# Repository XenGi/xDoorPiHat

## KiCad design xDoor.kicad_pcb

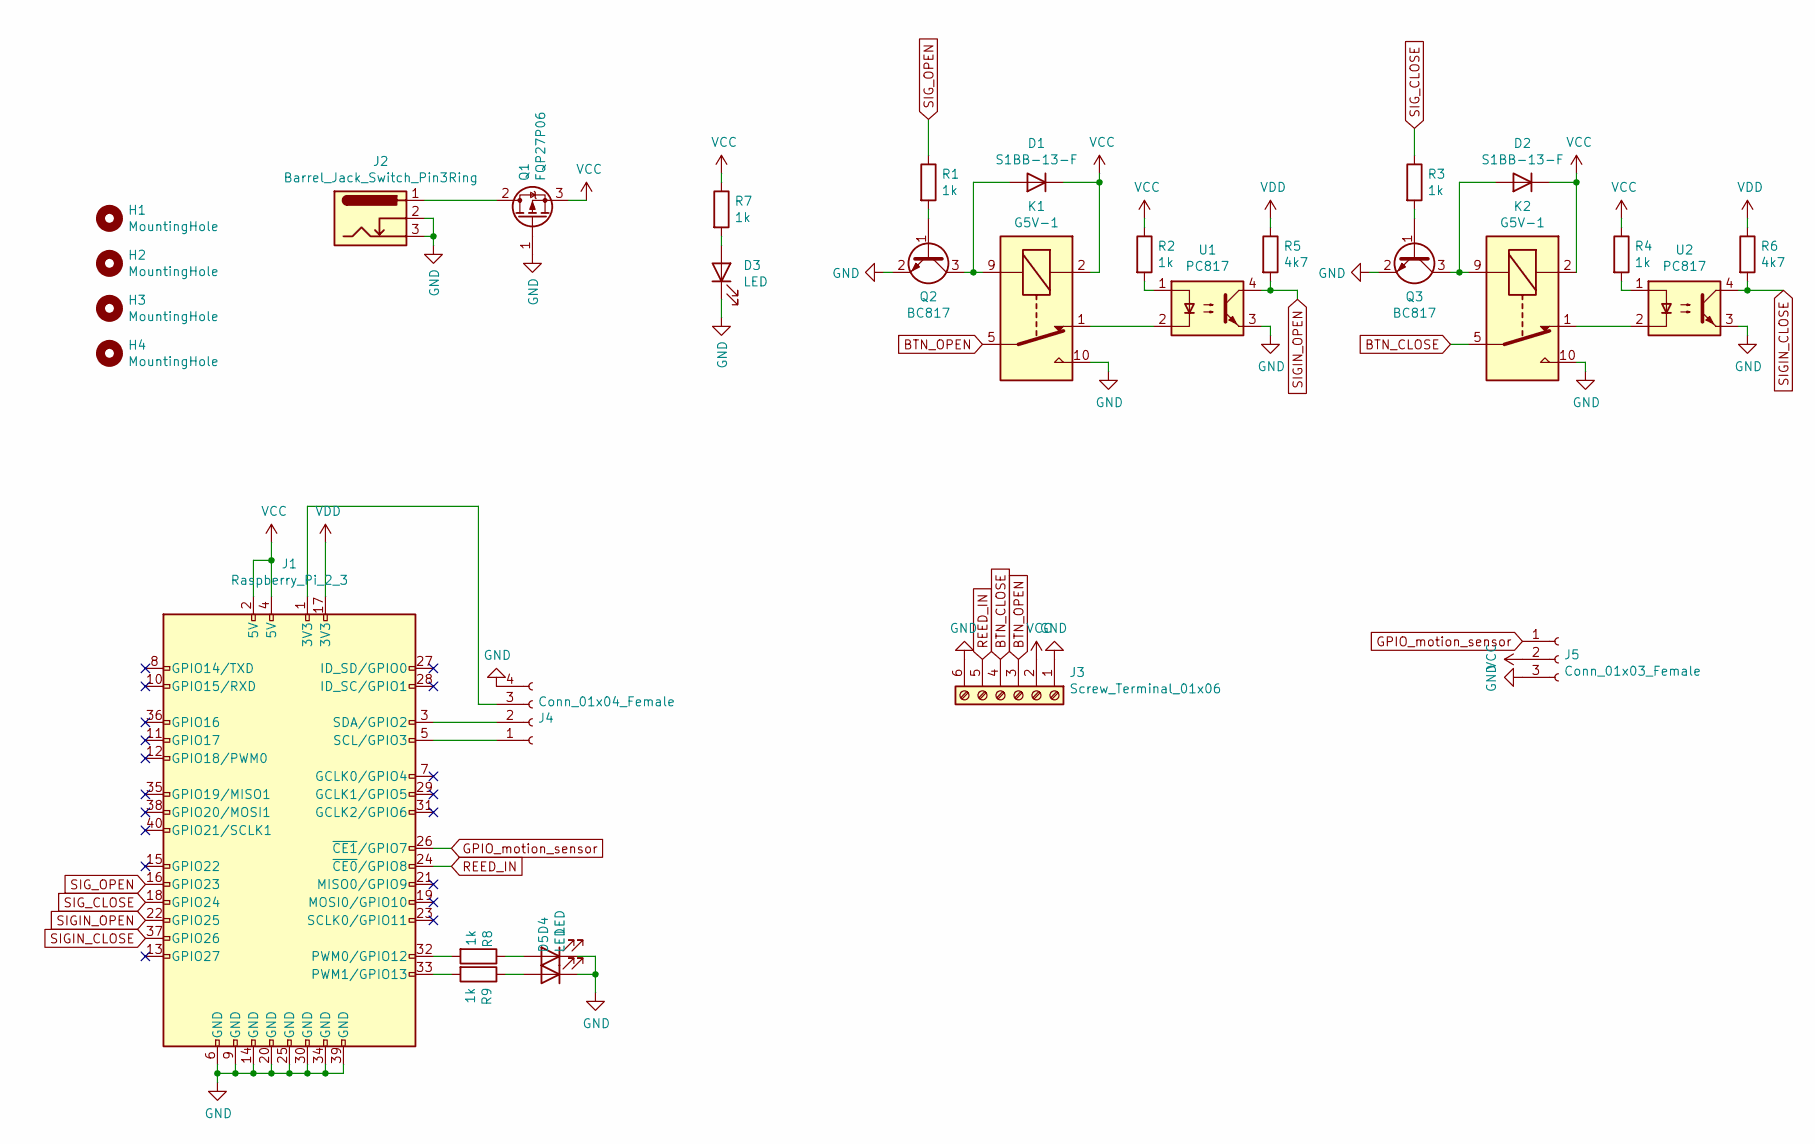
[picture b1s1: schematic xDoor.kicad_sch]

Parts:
D1, D2: S1BB-13-F; D_SMB_Handsoldering; mouser 621-RS1BB-13-F
D3: LED; LED_1206_3216Metric_Pad1.42x1.75mm_HandSolder; mouser 859-LTST-C230GKT
D4: LED; LED_1206_3216Metric_Pad1.42x1.75mm_HandSolder; mouser 859-LTST-C150EKT
D5: LED; LED_1206_3216Metric_Pad1.42x1.75mm_HandSolder; mouser 859-LTST-C250TBKT
H1, H2, H3, H4: MountingHole; MountingHole_2.7mm_M2.5_DIN965
J1: Raspberry_Pi_2_3; PinSocket_2x20_P2.54mm_Vertical
J2: Barrel_Jack_Switch_Pin3Ring; BarrelJack_Horizontal
J3: Screw_Terminal_01x06; TerminalBlock_bornier-6_P5.08mm; mouser 490-TB006-508-06BE
J4: Conn_01x04_Female; JST_SH_SM04B-SRSS-TB_1x04-1MP_P1.00mm_Horizontal
J5: Conn_01x03_Female; PinSocket_1x03_P2.54mm_Vertical
K1, K2: G5V-1; Relay_SPDT_Omron_G5V-1; mouser 653-G5V-1-DC5
Q1: FQP27P06; TO-263-2; mouser 512-FQP27P06
Q2, Q3: BC817; SOT-23; mouser 637-BC817-25
R1, R2, R3, R4, R7, R8, R9: 1k; R_1206_3216Metric_Pad1.30x1.75mm_HandSolder; mouser 279-CRGCQ1206F1K0
R5, R6: 4k7; R_1206_3216Metric_Pad1.30x1.75mm_HandSolder; mouser 791-WR12X4701FTL
U1, U2: PC817; DIP-4_W7.62mm; mouser 621-DPC817D-A-TU

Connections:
BTN_CLOSE: J3.4, K2.5, K2.6
BTN_OPEN: J3.3, K1.5, K1.6
GND: D3.1 (K), D4.1 (K), D5.1 (K), J1.6 (GND), J1.9 (GND), J1.14 (GND), J1.20 (GND), J1.25 (GND), J1.30 (GND), J1.34 (GND), J1.39 (GND), J2.2, J2.3, J3.1, J3.6, J4.4, J5.3, K1.10, K2.10, Q1.1 (G), Q2.2 (E), Q3.2 (E), U1.3, U2.3
GPIO_motion_sensor: J1.26 (~CE1/GPIO7), J5.1
unnamed: D1.2 (A), K1.9, Q2.3 (C)
unnamed: D2.2 (A), K2.9, Q3.3 (C)
unnamed: D3.2 (A), R7.2
unnamed: D4.2 (A), R8.1
unnamed: D5.2 (A), R9.1
unnamed: J1.32 (PWM0/GPIO12), R8.2
unnamed: J1.33 (PWM1/GPIO13), R9.2
unnamed: J1.5 (SCL/GPIO3), J4.1
unnamed: J1.3 (SDA/GPIO2), J4.2
unnamed: J1.1 (3V3), J4.3
unnamed: K1.1, U1.2
unnamed: K2.1, U2.2
unnamed: J2.1, Q1.2 (D)
unnamed: Q2.1 (B), R1.2
unnamed: Q3.1 (B), R3.2
unnamed: R2.2, U1.1
unnamed: R4.2, U2.1
REED_IN: J1.24 (~CE0/GPIO8), J3.5
SIGIN_CLOSE: J1.37 (GPIO26), R6.2, U2.4
SIGIN_OPEN: J1.22 (GPIO25), R5.2, U1.4
SIG_CLOSE: J1.18 (GPIO24), R3.1
SIG_OPEN: J1.16 (GPIO23), R1.1
VCC: D1.1 (K), D2.1 (K), J1.2 (5V), J1.4 (5V), J3.2, J5.2, K1.2, K2.2, Q1.3 (S), R2.1, R4.1, R7.1
VDD: J1.17 (3V3), R5.1, R6.1

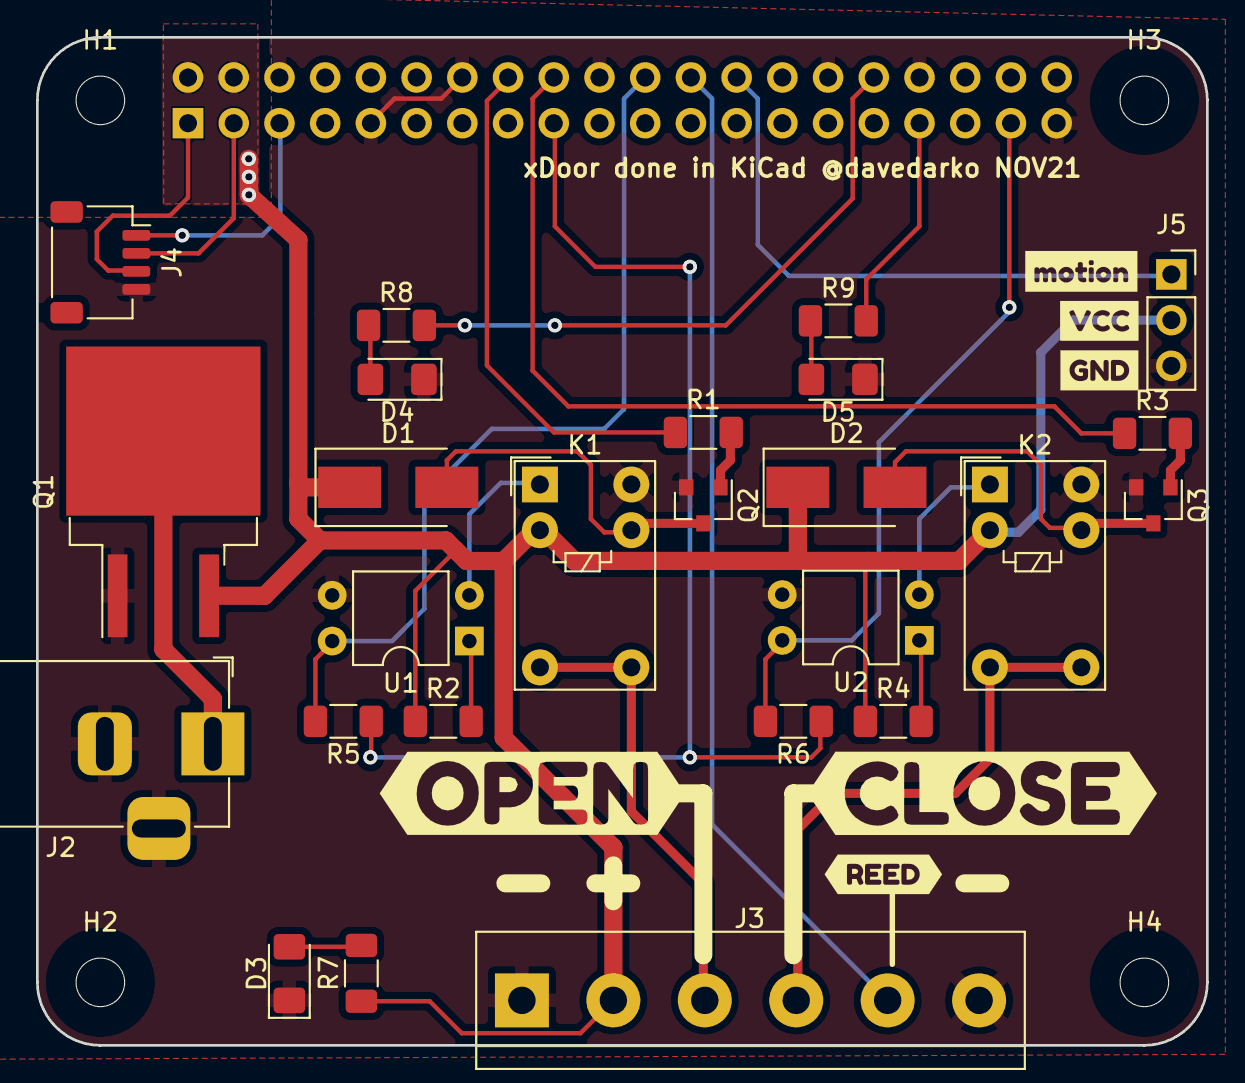
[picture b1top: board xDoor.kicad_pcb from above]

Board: 2 copper layers, 65.0 x 56.0 mm, 36 parts (1 on the bottom side), 28 nets.

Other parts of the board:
kibuzzard-61843A90, kibuzzard-61843AB1, kibuzzard-618517AA, kibuzzard-618517C8, kibuzzard-61850136, kibuzzard-61851795: G***; label

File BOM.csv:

"Reference","Qty","Value","DNP","Exclude from BOM","Exclude from Board","Footprint","Datasheet","mouser","lcsc"
"D1,D2","2","S1BB-13-F","","","","Diode_SMD:D_SMB_Handsoldering",""," 621-RS1BB-13-F ","C151322"
"D3,D4,D5","3","LED","","","","LED_SMD:LED_1206_3216Metric_Pad1.42x1.75mm_HandSolder","","859-LTST-C150EKT,859-LTST-C230GKT,859-LTST-C250TBKT","C2980185,C51933316,C7433006"
"H1,H2,H3,H4","4","MountingHole","","","","MountingHole:MountingHole_2.7mm_M2.5_DIN965","","",""
"J1","1","Raspberry_Pi_2_3","","","","Connector_PinSocket_2.54mm:PinSocket_2x20_P2.54mm_Vertical","https://www.raspberrypi.org/documentation/hardware/raspberry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","",""
"J2","1","Barrel_Jack_Switch_Pin3Ring","","","","Connector_BarrelJack:BarrelJack_Horizontal","","",""
"J3","1","Screw_Terminal_01x06","","","","TerminalBlock:TerminalBlock_bornier-6_P5.08mm","","490-TB006-508-06BE ","C22450486"
"J4","1","Conn_01x04_Female","","","","Connector_JST:JST_SH_SM04B-SRSS-TB_1x04-1MP_P1.00mm_Horizontal","","",""
"J5","1","Conn_01x03_Female","","","","Connector_PinSocket_2.54mm:PinSocket_1x03_P2.54mm_Vertical","","",""
"K1,K2","2","G5V-1","","","","Relay_THT:Relay_SPDT_Omron_G5V-1","http://omronfs.omron.com/en_US/ecb/products/pdf/en-g5v_1.pdf","653-G5V-1-DC5 ","C28695"
"Q1","1","FQP27P06","","","","Package_TO_SOT_SMD:TO-263-2","https://www.onsemi.com/pub/Collateral/FQP27P06-D.PDF"," 512-FQP27P06 ","C462764"
"Q2,Q3","2","BC817","","","","Package_TO_SOT_SMD:SOT-23","https://www.onsemi.com/pub/Collateral/BC818-D.pdf","637-BC817-25 ","C22400355"
"R1,R2,R3,R4,R7,R8,R9","7","1k","","","","Resistor_SMD:R_1206_3216Metric_Pad1.30x1.75mm_HandSolder",""," 279-CRGCQ1206F1K0 ","C164026"
"R5,R6","2","4k7","","","","Resistor_SMD:R_1206_3216Metric_Pad1.30x1.75mm_HandSolder","","791-WR12X4701FTL","C137262"
"U1,U2","2","PC817","","","","Package_DIP:DIP-4_W7.62mm","http://www.soselectronic.cz/a_info/resource/d/pc817.pdf","621-DPC817D-A-TU","C50229500"

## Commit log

2026-03-30 add part numbers from mouser and LCSC to BOM
